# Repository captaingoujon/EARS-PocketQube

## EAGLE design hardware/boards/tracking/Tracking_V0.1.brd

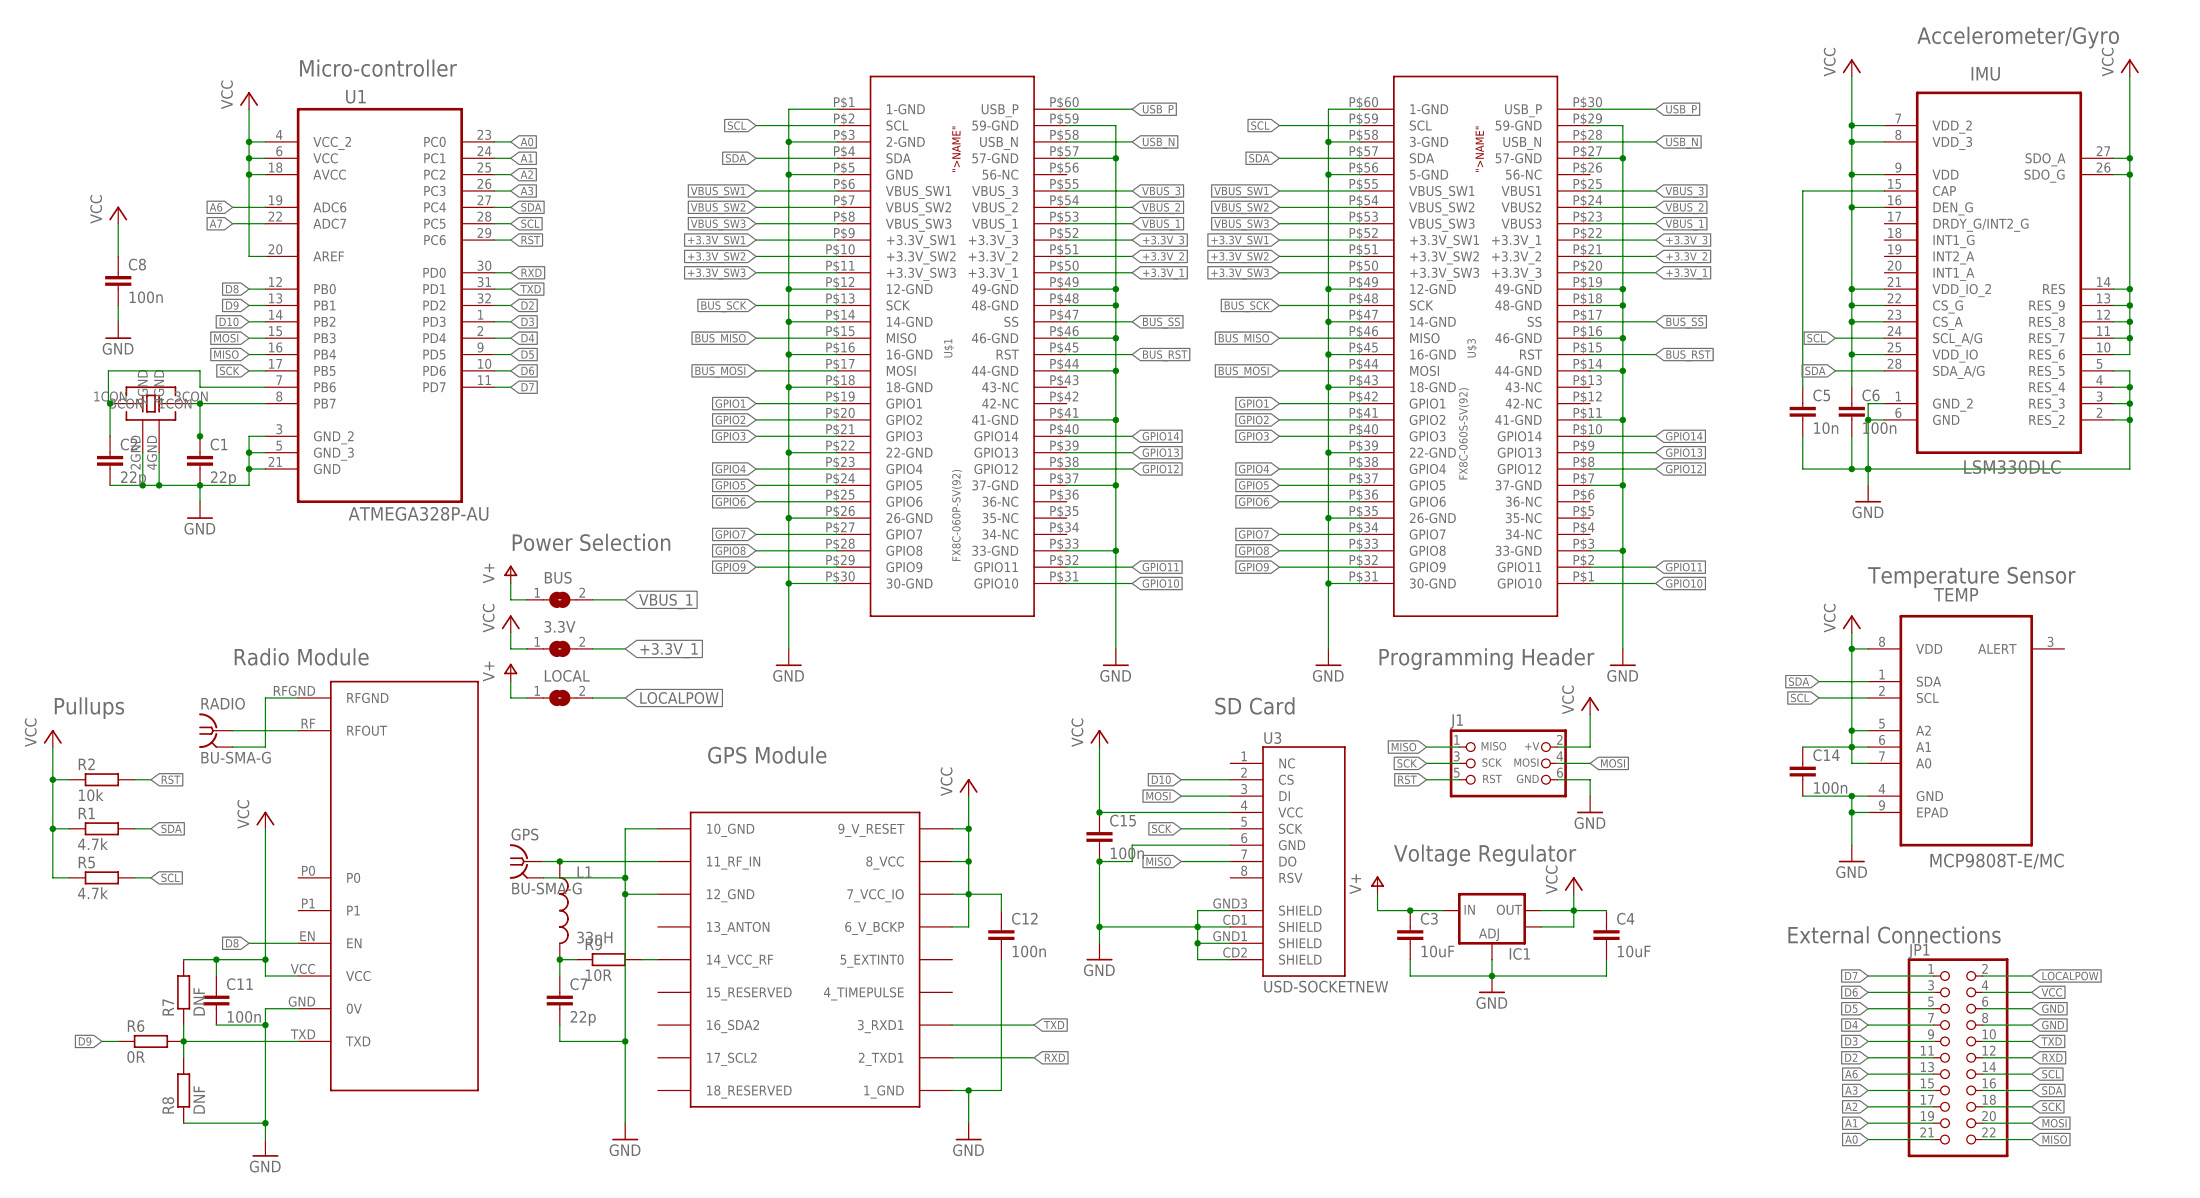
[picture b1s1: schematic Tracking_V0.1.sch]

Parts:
3.3V: SJ
BUS: SJ
C1, C2, C7: 22p; C0603
C3, C4: 10uF; C0603
C5: 10n; C0603
C6, C8, C11, C12, C14, C15: 100n; C0603
GPS: BU-SMA-G
IC1: V_REG_LM1117SOT223; SOT223
IMU: LSM330DLC; LGA28R50P6X8_400X500X110
J1: CON_HEADER_PRG_AVR_ICSP-PTH; HEADER_PRG_2X03
JP1: PINHD-2X11; 2X11
L1: 33nH; 0603
LOCAL: SJ
R1, R5: 4.7k; R0603
R2: 10k; R0603
R6: 0R; R0603
R7, R8: DNF; R0603
R9: 10R; R0603
RADIO: BU-SMA-G
TEMP: MCP9808T-E/MC; DFN300X200X100-9N
U1: ATMEGA328P-AU; QFP80P900X900X120-32N
U3: USD-SOCKETNEW; MICRO-SD-SOCKET-PP
U$1: FX8C-060P-SV(92)
U$2: CRYSTAL
U$3: FX8C-060S-SV(92)
U$4: UBLOX_MAX
U$6: RADIOMETRIX-MTX2

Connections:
+3.3V_1: 3.3V.2, U$1.P$50 (+3.3V_1), U$3.P$20 (+3.3V_3)
+3.3V_2: U$1.P$51 (+3.3V_2), U$3.P$21 (+3.3V_2)
+3.3V_3: U$1.P$52 (+3.3V_3), U$3.P$22 (+3.3V_1)
+3.3V_SW1: U$1.P$9 (+3.3V_SW1), U$3.P$52 (+3.3V_SW1)
+3.3V_SW2: U$1.P$10 (+3.3V_SW2), U$3.P$51 (+3.3V_SW2)
+3.3V_SW3: U$1.P$11 (+3.3V_SW3), U$3.P$50 (+3.3V_SW3)
A0: JP1.21, U1.23 (PC0)
A1: JP1.19, U1.24 (PC1)
A2: JP1.17, U1.25 (PC2)
A3: JP1.15, U1.26 (PC3)
A6: JP1.13, U1.19 (ADC6)
A7: U1.22 (ADC7)
BUS_MISO: U$1.P$15 (MISO), U$3.P$46 (MISO)
BUS_MOSI: U$1.P$17 (MOSI), U$3.P$44 (MOSI)
BUS_RST: U$1.P$45 (RST), U$3.P$15 (RST)
BUS_SCK: U$1.P$13 (SCK), U$3.P$48 (SCK)
BUS_SS: U$1.P$47 (SS), U$3.P$17 (SS)
D2: JP1.11, U1.32 (PD2)
D3: JP1.9, U1.1 (PD3)
D4: JP1.7, U1.2 (PD4)
D5: JP1.5, U1.9 (PD5)
D6: JP1.3, U1.10 (PD6)
D7: JP1.1, U1.11 (PD7)
D8: U1.12 (PB0), U$6.EN
D9: R6.1, U1.13 (PB1)
D10: U1.14 (PB2), U3.2 (CS)
GND: C1.2, C2.2, C3.2, C4.2, C5.2, C6.2, C7.2, C8.2, C11.2, C12.2, C14.2, C15.2, GPS.2, GPS.3 (2), GPS.4 (2), GPS.5 (2), IC1.1 (ADJ), IMU.1 (GND_2), IMU.2 (RES_2), IMU.3 (RES_3), IMU.4 (RES_4), IMU.5 (RES_5), IMU.6 (GND), J1.6 (GND), JP1.6, JP1.8, R8.1, TEMP.4 (GND), TEMP.9 (EPAD), U1.3 (GND_2), U1.5 (GND_3), U1.21 (GND), U3.6 (GND), U3.CD1 (SHIELD), U3.CD2 (SHIELD), U3.GND1 (SHIELD), U3.GND3 (SHIELD), U$1.P$1 (1-GND), U$1.P$3 (2-GND), U$1.P$5 (GND), U$1.P$12 (12-GND), U$1.P$14 (14-GND), U$1.P$16 (16-GND), U$1.P$18 (18-GND), U$1.P$22 (22-GND), U$1.P$26 (26-GND), U$1.P$30 (30-GND), U$1.P$33 (33-GND), U$1.P$37 (37-GND), U$1.P$41 (41-GND), U$1.P$44 (44-GND), U$1.P$46 (46-GND), U$1.P$48 (48-GND), U$1.P$49 (49-GND), U$1.P$57 (57-GND), U$1.P$59 (59-GND), U$2.2GND, U$2.4GND, U$3.P$3 (33-GND), U$3.P$7 (37-GND), U$3.P$11 (41-GND), U$3.P$14 (44-GND), U$3.P$16 (46-GND), U$3.P$18 (48-GND), U$3.P$19 (49-GND), U$3.P$27 (57-GND), U$3.P$29 (59-GND), U$3.P$31 (30-GND), U$3.P$35 (26-GND), U$3.P$39 (22-GND), U$3.P$43 (18-GND), U$3.P$45 (16-GND), U$3.P$47 (14-GND), U$3.P$49 (12-GND), U$3.P$56 (5-GND), U$3.P$58 (3-GND), U$3.P$60 (1-GND), U$4.1_GND, U$4.10_GND, U$4.12_GND, U$6.GND (0V)
GPIO1: U$1.P$19 (GPIO1), U$3.P$42 (GPIO1)
GPIO2: U$1.P$20 (GPIO2), U$3.P$41 (GPIO2)
GPIO3: U$1.P$21 (GPIO3), U$3.P$40 (GPIO3)
GPIO4: U$1.P$23 (GPIO4), U$3.P$38 (GPIO4)
GPIO5: U$1.P$24 (GPIO5), U$3.P$37 (GPIO5)
GPIO6: U$1.P$25 (GPIO6), U$3.P$36 (GPIO6)
GPIO7: U$1.P$27 (GPIO7), U$3.P$34 (GPIO7)
GPIO8: U$1.P$28 (GPIO8), U$3.P$33 (GPIO8)
GPIO9: U$1.P$29 (GPIO9), U$3.P$32 (GPIO9)
GPIO10: U$1.P$31 (GPIO10), U$3.P$1 (GPIO10)
GPIO11: U$1.P$32 (GPIO11), U$3.P$2 (GPIO11)
GPIO12: U$1.P$38 (GPIO12), U$3.P$8 (GPIO12)
GPIO13: U$1.P$39 (GPIO13), U$3.P$9 (GPIO13)
GPIO14: U$1.P$40 (GPIO14), U$3.P$10 (GPIO14)
LOCALPOW: JP1.2, LOCAL.2
MISO: J1.1 (MISO), JP1.22, U1.16 (PB4), U3.7 (DO)
MOSI: J1.4 (MOSI), JP1.20, U1.15 (PB3), U3.3 (DI)
unnamed: GPS.1, L1.1, U$4.11_RF_IN
unnamed: C1.1, U1.8 (PB7), U$2.3CON
unnamed: R9.2, U$4.14_VCC_RF
unnamed: C2.1, U1.7 (PB6), U$2.1CON
unnamed: RADIO.1, U$6.RF (RFOUT)
unnamed: R6.2, R7.1, R8.2, U$6.TXD
unnamed: C7.1, L1.2, R9.1
unnamed: C5.1, IMU.15 (CAP)
RFGND: RADIO.2, RADIO.3 (2), RADIO.4 (2), RADIO.5 (2), U$6.RFGND
RST: J1.5 (RST), R2.2, U1.29 (PC6)
RXD: JP1.12, U1.30 (PD0), U$4.2_TXD1
SCK: J1.3 (SCK), JP1.18, U1.17 (PB5), U3.5 (SCK)
SCL: IMU.24 (SCL_A/G), JP1.14, R5.2, TEMP.2 (SCL), U1.28 (PC5), U$1.P$2 (SCL), U$3.P$59 (SCL)
SDA: IMU.28 (SDA_A/G), JP1.16, R1.2, TEMP.1 (SDA), U1.27 (PC4), U$1.P$4 (SDA), U$3.P$57 (SDA)
TXD: JP1.10, U1.31 (PD1), U$4.3_RXD1
USB_N: U$1.P$58 (USB_N), U$3.P$28 (USB_N)
USB_P: U$1.P$60 (USB_P), U$3.P$30 (USB_P)
V+: BUS.1, C3.1, IC1.3 (IN), LOCAL.1
VBUS_1: BUS.2, U$1.P$53 (VBUS_1), U$3.P$23 (VBUS3)
VBUS_2: U$1.P$54 (VBUS_2), U$3.P$24 (VBUS2)
VBUS_3: U$1.P$55 (VBUS_3), U$3.P$25 (VBUS1)
VBUS_SW1: U$1.P$6 (VBUS_SW1), U$3.P$55 (VBUS_SW1)
VBUS_SW2: U$1.P$7 (VBUS_SW2), U$3.P$54 (VBUS_SW2)
VBUS_SW3: U$1.P$8 (VBUS_SW3), U$3.P$53 (VBUS_SW3)
VCC: 3.3V.1, C4.1, C6.1, C8.1, C11.1, C12.1, C14.1, C15.1, IC1.2 (OUT), IC1.4 (OUT), IMU.7 (VDD_2), IMU.8 (VDD_3), IMU.9 (VDD), IMU.10 (RES_6), IMU.11 (RES_7), IMU.12 (RES_8), IMU.13 (RES_9), IMU.14 (RES), IMU.16 (DEN_G), IMU.21 (VDD_IO_2), IMU.22 (CS_G), IMU.23 (CS_A), IMU.25 (VDD_IO), IMU.26 (SDO_G), IMU.27 (SDO_A), J1.2 (+V), JP1.4, R1.1, R2.1, R5.1, R7.2, TEMP.5 (A2), TEMP.6 (A1), TEMP.7 (A0), TEMP.8 (VDD), U1.4 (VCC_2), U1.6 (VCC), U1.18 (AVCC), U1.20 (AREF), U3.4 (VCC), U$4.6_V_BCKP, U$4.7_VCC_IO, U$4.8_VCC, U$4.9_V_RESET, U$6.VCC

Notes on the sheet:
Micro-controller
Programming Header
Pullups
Voltage Regulator
Power Selection
GPS Module
Radio Module
SD Card
Temperature Sensor
Accelerometer/Gyro
External Connections

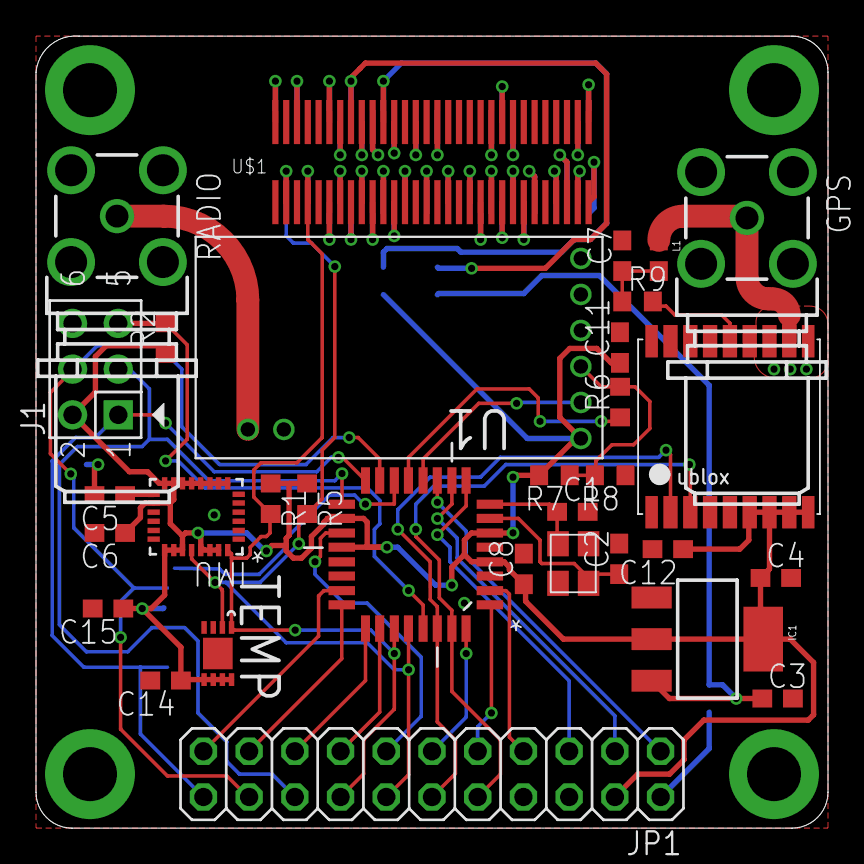
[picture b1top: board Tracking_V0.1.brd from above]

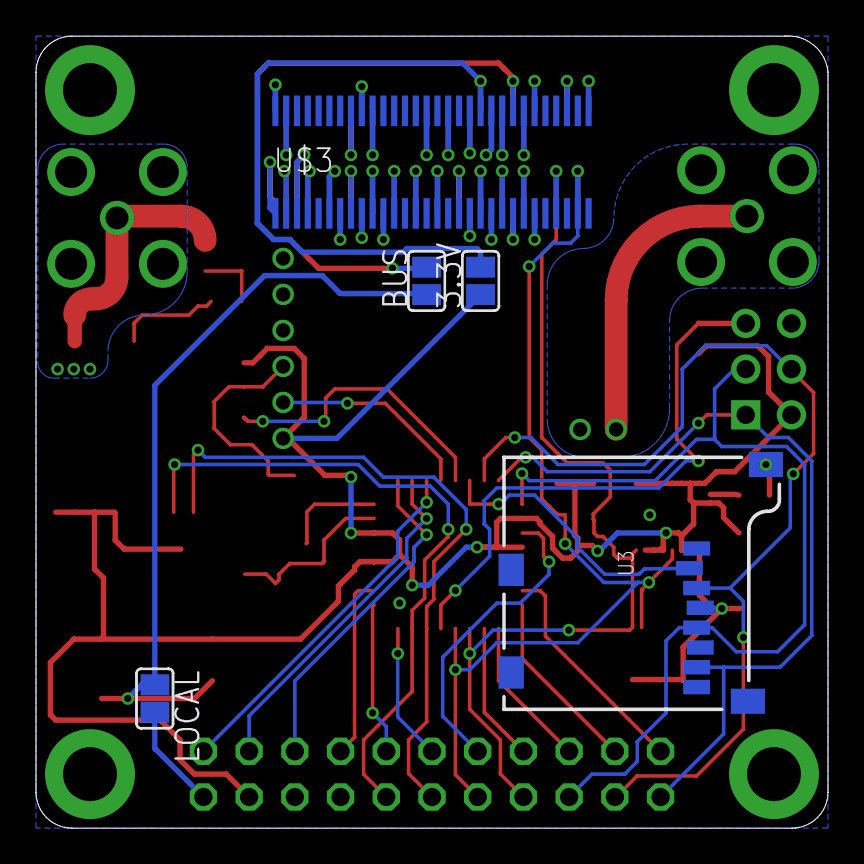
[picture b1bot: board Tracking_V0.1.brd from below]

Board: 4 copper layers, 44.0 x 44.0 mm, 37 parts (5 on the bottom side), 68 nets.

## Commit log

2014-12-28 Created Tracking board, matches version D of HAB Computer
2014-12-28 Added board images
2014-12-28 Switched to right angle SMA connectors, created 3d render
2014-12-28 Added renders of template board

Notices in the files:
parts and their libraries:
SparkFun: Licensing: CC v3.0 Share-Alike You are welcome to use this library for commercial purposes.
SparkFun-Aesthetics: Licensing: Creative Commons ShareAlike 4.0 International - https://creativecommons.org/licenses/by-sa/4.0
